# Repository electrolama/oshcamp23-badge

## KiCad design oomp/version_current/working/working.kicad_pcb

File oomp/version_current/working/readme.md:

# oshcamp23-badge by electrolama  
This is a harvested standardized copy of a project from github.  
The original project can be found at:  
https://github.com/electrolama/oshcamp23-badge  
Please consult that link for additional, details, files, and license information.  
Note: It was auto harvested and if the original repo had more than one board file or anything out of the ordinary the files here are likely not representative.

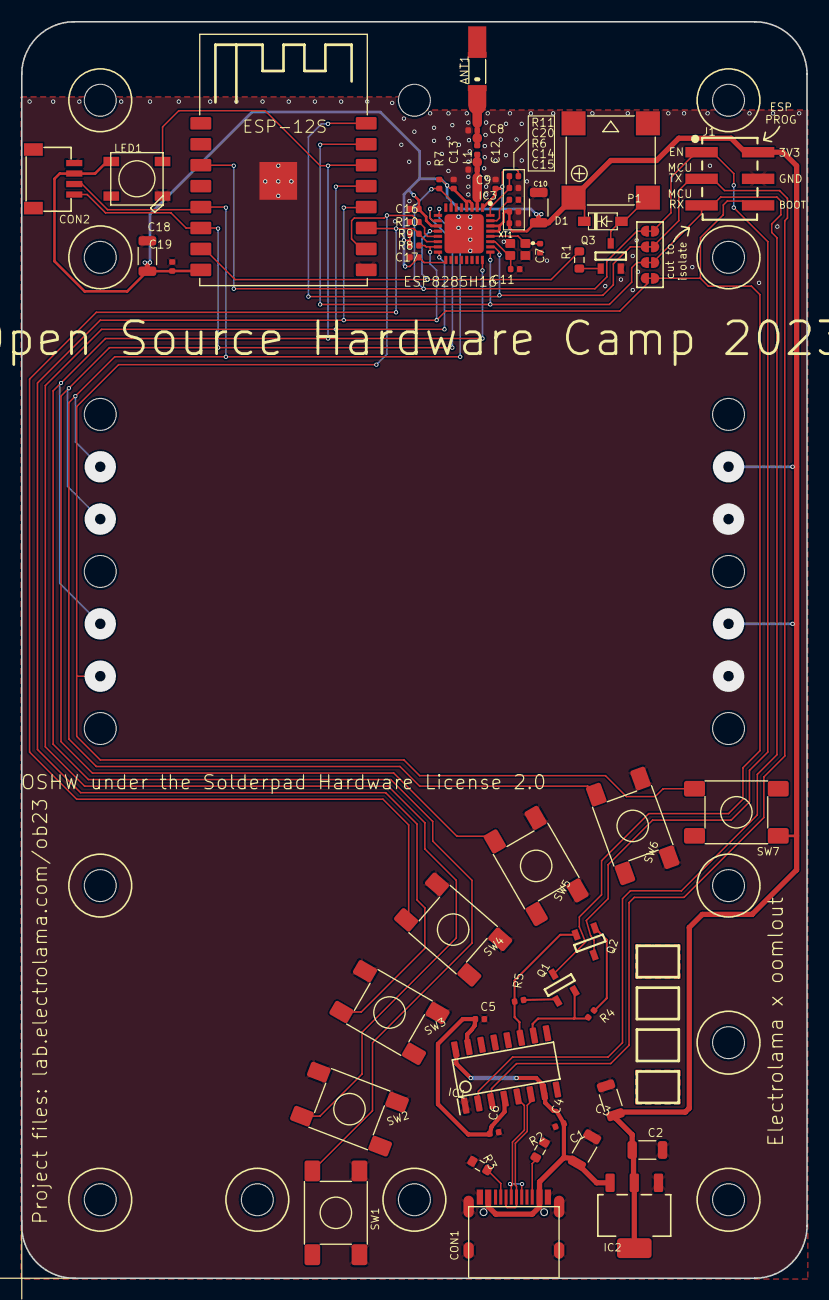
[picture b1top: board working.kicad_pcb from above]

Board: 2 copper layers, 75.0 x 120.0 mm, 76 parts (0 on the bottom side), 35 nets.

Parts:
@HOLE0, @HOLE1, @HOLE2, @HOLE3, @HOLE4, @HOLE5, @HOLE6, @HOLE7, @HOLE8, @HOLE9, @HOLE10, @HOLE11, @HOLE12, @HOLE13, @HOLE14, @HOLE15, @HOLE16, @HOLE17: (no value)
ANT1: ANT3216LL00R2400A; YAGEO-ANT3216LL00R2400A
C1, C2, C3, C10, C18: 47u; _PKG_C_1206
C4, C5, C6, C19: 100n; _PKG_C_0402
C7, C11: 8p; _PKG_C_0402
C8, C9: TBD; _PKG_C_0402_NOTHERMALS
C12, C14: 4u7; _PKG_C_0402_NOTHERMALS
C13, C15, C16, C17, C20: 100n; _PKG_C_0402_NOTHERMALS
CON1: USBC_C-31-M-12
CON2: STEMMA_I2C_QT; JST_SH4
D1: _PKG_SOD123
IC1: _PKG_SOP16
IC2: LD1117-3.3; _PKG_SOT223-4_TI-DCY4
IC3: WMCU-ESP8285H16; QFN50P500X500X90-33N
J1: 61030621121
L1: TBD; _PKG_L_0402
LED1: WS2812B5050; WS2812B
MOD1: ESP-12S
P1: Buzzer; MLT-8530
Q1, Q2, Q3: SS8050; SOT96P237X111-3N
R1: 220; _PKG_R_0603
R2, R3: 5k1; _PKG_R_0603
R4, R5, R6, R7, R8, R9, R10, R11: 12k 1%; _PKG_R_0402
SJ1, SJ2, SJ3, SJ4: SJ-SHORT
SW1, SW2, SW3, SW4, SW5, SW6, SW7: GENERIC_SPNO_4P_6X6MM
XT1: 26MHz; XTAL-4P-2016

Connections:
ANT: C9.2, IC3.2, L1.2
ANT': ANT1.S1, C8.2, L1.1
AUTORST_BOOT: J1.6, Q1.3, SJ4.1
AUTORST_EN: J1.1, Q2.3, SJ1.2
CH343_3V: C5.1, C6.1, IC1.4, IC1.15
DTR: IC1.10, Q1.2, R4.1
EN: IC3.7, MOD1.EN, R7.2, SJ1.1
GND: C1.2, C2.2, C3.2, C4.2, C5.2, C6.2, C7.1, C8.1, C9.1, C10.2, C11.1, C12.1, C13.1, C14.1, C15.1, C16.1, C17.1, C18.2, C19.2, C20.1, CON1.GND@1, CON1.GND@2, CON1.P$1, CON1.P$2, CON1.P$3, CON1.P$4, CON1.P$5, CON1.P$6, CON1.P$7, CON1.P$8, CON2.1, IC1.1, IC2.1, IC3.33, J1.4, LED1.3-GND, MOD1.EPAD, MOD1.GND, Q3.2, R2.1, R3.1, R6.2, R10.1, SW1.P$3, SW1.P$4, SW2.P$3, SW2.P$4, SW3.P$3, SW3.P$4, SW4.P$3, SW4.P$4, SW5.P$3, SW5.P$4, SW6.P$3, SW6.P$4, XT1.2, XT1.4
IO0: IC3.15, MOD1.IO0, R8.2, SJ4.2, SW3.P$1, SW3.P$2
IO1_TX: IC3.26, MOD1.TXD/IO1, SJ2.1
IO2: IC3.14, MOD1.IO2, R9.2, SW4.P$1, SW4.P$2
IO3_RX: IC3.25, MOD1.RXD/IO3, SJ3.1
IO4: IC3.16, MOD1.IO4, SW2.P$1, SW2.P$2
IO5: IC3.24, LED1.4-DIN, MOD1.IO5, SW1.P$1, SW1.P$2
IO12: CON2.4, IC3.10, MOD1.IO12, SW5.P$1, SW5.P$2
IO13: IC3.12, MOD1.IO13, R1.2
IO14: CON2.3, IC3.9, MOD1.IO14, SW6.P$1, SW6.P$2
IO15: IC3.13, MOD1.IO15, R10.2, SW7.P$1, SW7.P$2
unnamed: Q1.1, R5.1
unnamed: IC3.31, R6.1
unnamed: D1.2, P1.-, Q3.3
unnamed: Q2.1, R4.2
unnamed: CON1.CC1, R3.2
unnamed: CON1.CC2, R2.2
unnamed: Q3.1, R1.1
PC_RX: IC1.3, J1.3, SJ2.2
PC_TX: IC1.2, J1.5, SJ3.2
RST_C: C20.2, IC3.32, R11.1
RTS: IC1.11, Q2.2, R5.2
USB_N: CON1.DN1, CON1.DN2, IC1.6
USB_P: CON1.DP1, CON1.DP2, IC1.5
VCC: C2.1, C3.1, C10.1, C12.2, C13.2, C14.2, C15.2, C16.2, C17.2, C18.1, C19.1, CON2.2, D1.1, IC2.2, IC2.4, IC3.1, IC3.3, IC3.4, IC3.11, IC3.17, IC3.29, IC3.30, J1.2, LED1.1-VDD, MOD1.VCC, P1.+, R7.1, R8.1, R9.1, R11.2, SW7.P$3, SW7.P$4
VUSB: C1.1, C4.1, CON1.VBUS@1, CON1.VBUS@2, IC1.7, IC1.16, IC2.3
XTAL_IN: C7.2, IC3.28, XT1.1
XTAL_OUT: C11.2, IC3.27, XT1.3

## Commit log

2023-08-06 add LICENSE and ignores
2023-08-06 initial commit for badge RevA2 EAGLE files and schematic PDF
2023-08-06 add refs
2023-08-06 add production files for badge RevA2
2023-08-06 add topper RevA1
2023-08-06 initial commit for Arduino hardware test fw
2023-08-06 added decorations and images
2023-08-07 added oomp generations
2023-08-07 added mechanical generations
2023-08-07 mechanical drawing
2023-08-07 better oomp gens and fixed adapter.
2023-08-07 removed silly dxf issues
2023-08-08 added oomp_yaml
2023-08-08 fixed oomp.yaml
2023-08-23 placeholder for docs
2023-08-26 add iboms for both kit variants
2023-08-26 initial commit for pages enabled branch
2023-08-26 update index
2023-08-26 add a bit of style
2023-08-26 add pcb pngs
2023-08-26 add more links
2023-08-26 update pcb front higher res now
2023-08-26 link to pages

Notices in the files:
oomp/version_current/working/working.kicad_pcb:
OSHW under the Solderpad Hardware License 2.0
